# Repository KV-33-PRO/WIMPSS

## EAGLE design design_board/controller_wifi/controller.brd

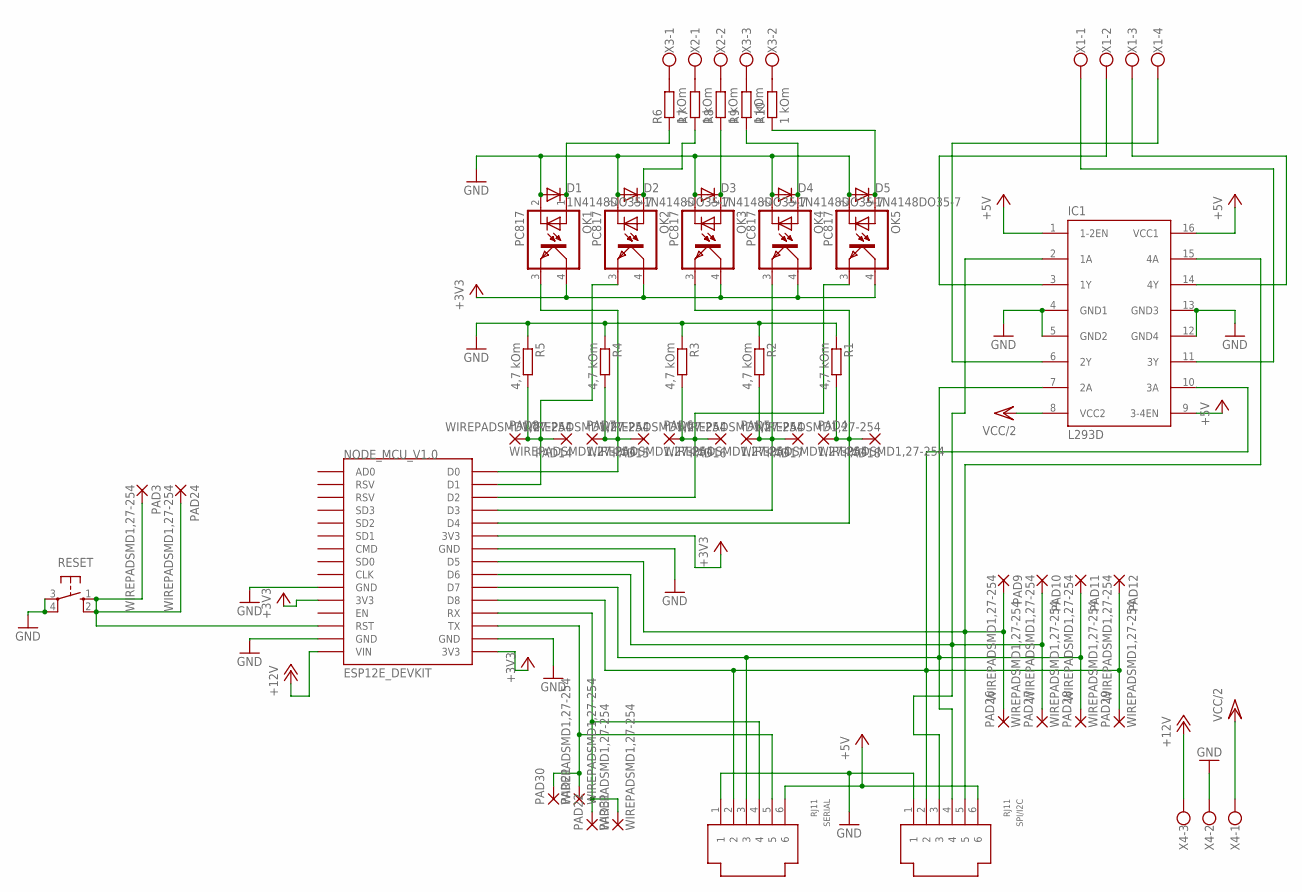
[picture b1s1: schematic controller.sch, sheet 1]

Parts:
D1, D2, D3, D4, D5: 1N4148DO35-7; DO35-7
IC1: L293D; DIL16
NODE_MCU_V1.0: ESP12E_DEVKIT
OK1, OK2, OK3, OK4, OK5: PC817; DIL04
PAD3, PAD4, PAD5, PAD6, PAD7, PAD8, PAD9, PAD10, PAD11, PAD12, PAD14, PAD15, PAD16, PAD17, PAD18, PAD21, PAD22, PAD24, PAD26, PAD27, PAD28, PAD29, PAD30, PAD31: WIREPADSMD1,27-254; SMD1,27-2,54
R1, R2, R3, R4, R5: 4,7 kOm; 0204/5
R6, R7, R8, R9, R10: 1 kOm; 0204V
RESET: 10-XX; B3F-10XX
SERIAL: RJ11
SPI/I2C: RJ11
X1: W237-4
X2: W237-102
X3, X4: W237-103

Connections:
+3V3: NODE_MCU_V1.0.3V3@0 (3V3), NODE_MCU_V1.0.3V3@1 (3V3), NODE_MCU_V1.0.3V3@2 (3V3), OK1.4 (COL), OK2.4 (COL), OK3.4 (COL), OK4.4 (COL), OK5.4 (COL); also elsewhere on the board
+5V: IC1.1 (1-2EN), IC1.9 (3-4EN), IC1.16 (VCC1), SERIAL.6, SPI/I2C.6; also elsewhere on the board
+12V: NODE_MCU_V1.0.VIN, X4.3; also elsewhere on the board
GND: D1.A, D2.A, D3.A, D4.A, D5.A, IC1.4 (GND1), IC1.5 (GND2), IC1.12 (GND4), IC1.13 (GND3), NODE_MCU_V1.0.GND@0 (GND), NODE_MCU_V1.0.GND@1 (GND), NODE_MCU_V1.0.GND@2 (GND), NODE_MCU_V1.0.GND@3 (GND), OK1.2 (C), OK2.2 (C), OK3.2 (C), OK4.2 (C), OK5.2 (C), R1.1, R2.1, R3.1, R4.1, R5.1, RESET.3, RESET.4 (P1), SERIAL.1, SPI/I2C.1, X4.2; also elsewhere on the board
unnamed: D4.C, OK4.1 (A), R9.1
unnamed: NODE_MCU_V1.0.D4, OK3.3 (EMIT), PAD4.1, PAD18.1, R1.2
unnamed: NODE_MCU_V1.0.D3, OK4.3 (EMIT), PAD5.1, PAD17.1, R2.2
unnamed: NODE_MCU_V1.0.D2, OK5.3 (EMIT), PAD6.1, PAD16.1, R3.2
unnamed: NODE_MCU_V1.0.D0, OK1.3 (EMIT), PAD7.1, PAD15.1, R4.2
unnamed: NODE_MCU_V1.0.D1, OK2.3 (EMIT), PAD8.1, PAD14.1, R5.2
unnamed: D2.C, OK2.1 (A), R7.1
unnamed: NODE_MCU_V1.0.RX, PAD22.1, PAD31.1, SERIAL.4
unnamed: D3.C, OK3.1 (A), R8.1
unnamed: R8.2, X2.2
unnamed: D5.C, OK5.1 (A), R10.1
unnamed: IC1.6 (2Y), X1.4
unnamed: IC1.7 (2A), NODE_MCU_V1.0.D7, PAD11.1, PAD28.1, SERIAL.3, SPI/I2C.4
unnamed: IC1.3 (1Y), X1.2
unnamed: IC1.10 (3A), NODE_MCU_V1.0.D8, PAD12.1, PAD29.1, SERIAL.2, SPI/I2C.2
unnamed: NODE_MCU_V1.0.TX, PAD21.1, PAD30.1, SERIAL.5
unnamed: IC1.2 (1A), NODE_MCU_V1.0.D6, PAD10.1, PAD27.1, SPI/I2C.3
unnamed: NODE_MCU_V1.0.RST, PAD3.1, PAD24.1, RESET.1 (S), RESET.2 (S1)
unnamed: IC1.15 (4A), NODE_MCU_V1.0.D5, PAD9.1, PAD26.1, SPI/I2C.5
unnamed: IC1.11 (3Y), X1.1
unnamed: IC1.14 (4Y), X1.3
unnamed: D1.C, OK1.1 (A), R6.1
unnamed: R7.2, X2.1
unnamed: R9.2, X3.3
unnamed: R10.2, X3.2
unnamed: R6.2, X3.1
VCC/2: IC1.8 (VCC2), X4.1; also elsewhere on the board

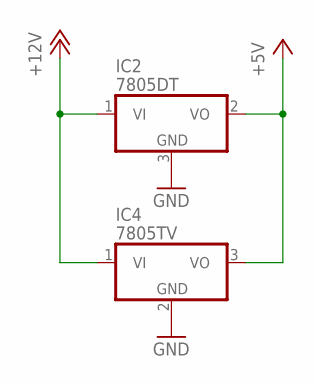
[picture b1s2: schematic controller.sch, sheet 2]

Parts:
IC2: 7805DT; TO252
IC4: 7805TV; TO220V

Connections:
+5V: IC2.2 (VO), IC4.3 (VO); also elsewhere on the board
+12V: IC2.1 (VI), IC4.1 (VI); also elsewhere on the board
GND: IC2.3 (GND), IC4.2 (GND); also elsewhere on the board

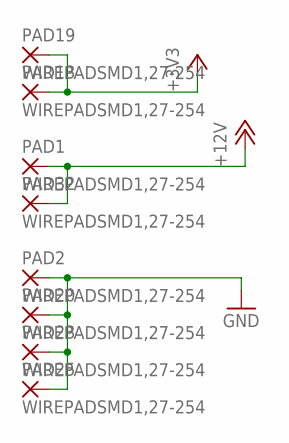
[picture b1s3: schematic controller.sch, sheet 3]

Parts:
PAD1, PAD2, PAD13, PAD19, PAD20, PAD23, PAD25, PAD32: WIREPADSMD1,27-254; SMD1,27-2,54

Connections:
+3V3: PAD13.1, PAD19.1; also elsewhere on the board
+12V: PAD1.1, PAD32.1; also elsewhere on the board
GND: PAD2.1, PAD20.1, PAD23.1, PAD25.1; also elsewhere on the board

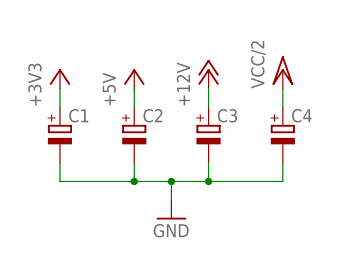
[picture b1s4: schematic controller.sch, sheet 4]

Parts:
C1, C2, C3, C4: CPOL-EUE2.5-5; E2,5-5

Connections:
+3V3: C1.+; also elsewhere on the board
+5V: C2.+; also elsewhere on the board
+12V: C3.+; also elsewhere on the board
GND: C1.-, C2.-, C3.-, C4.-; also elsewhere on the board
VCC/2: C4.+; also elsewhere on the board

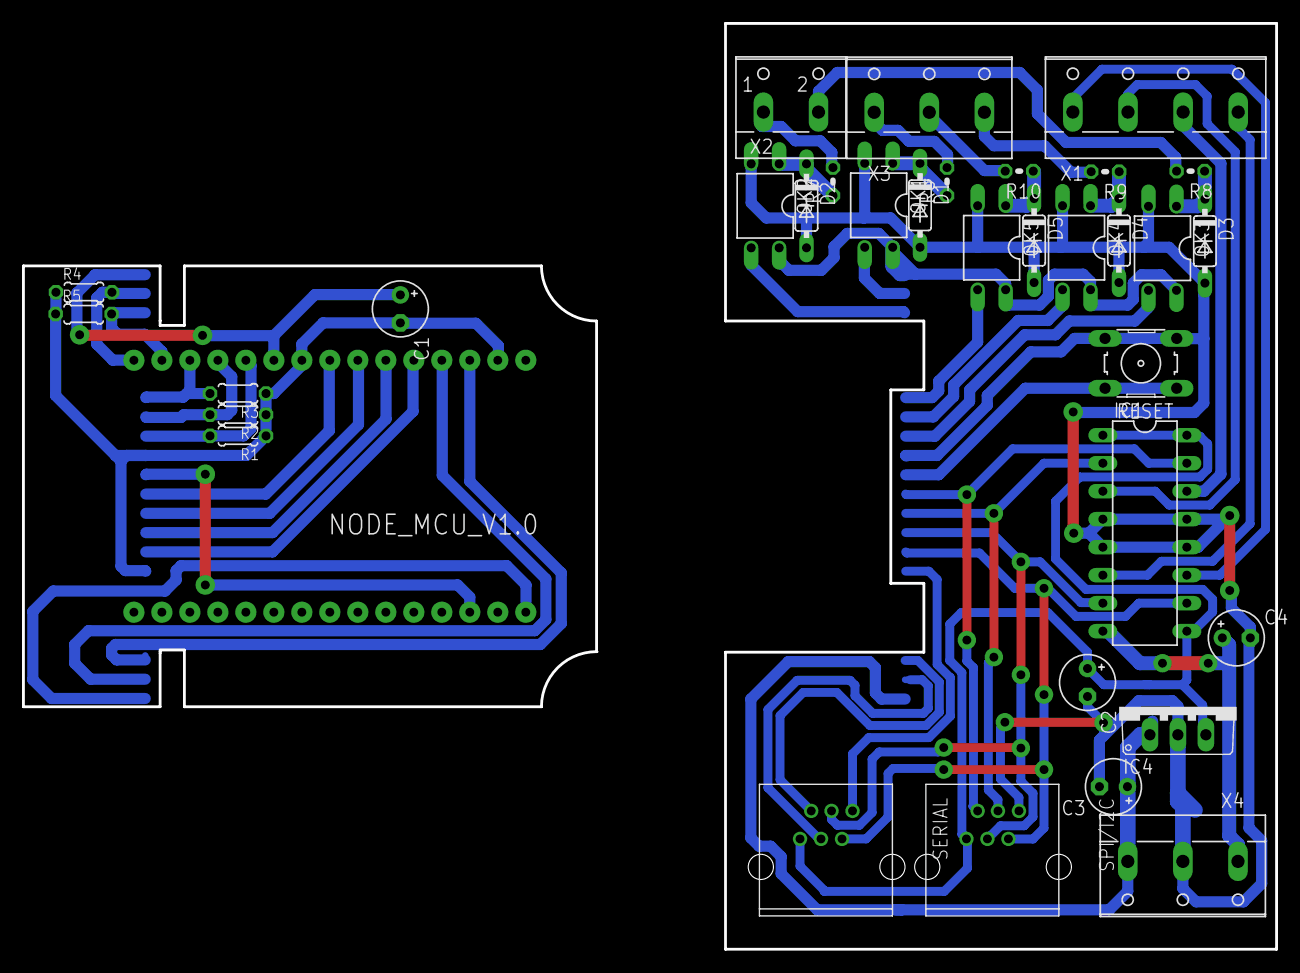
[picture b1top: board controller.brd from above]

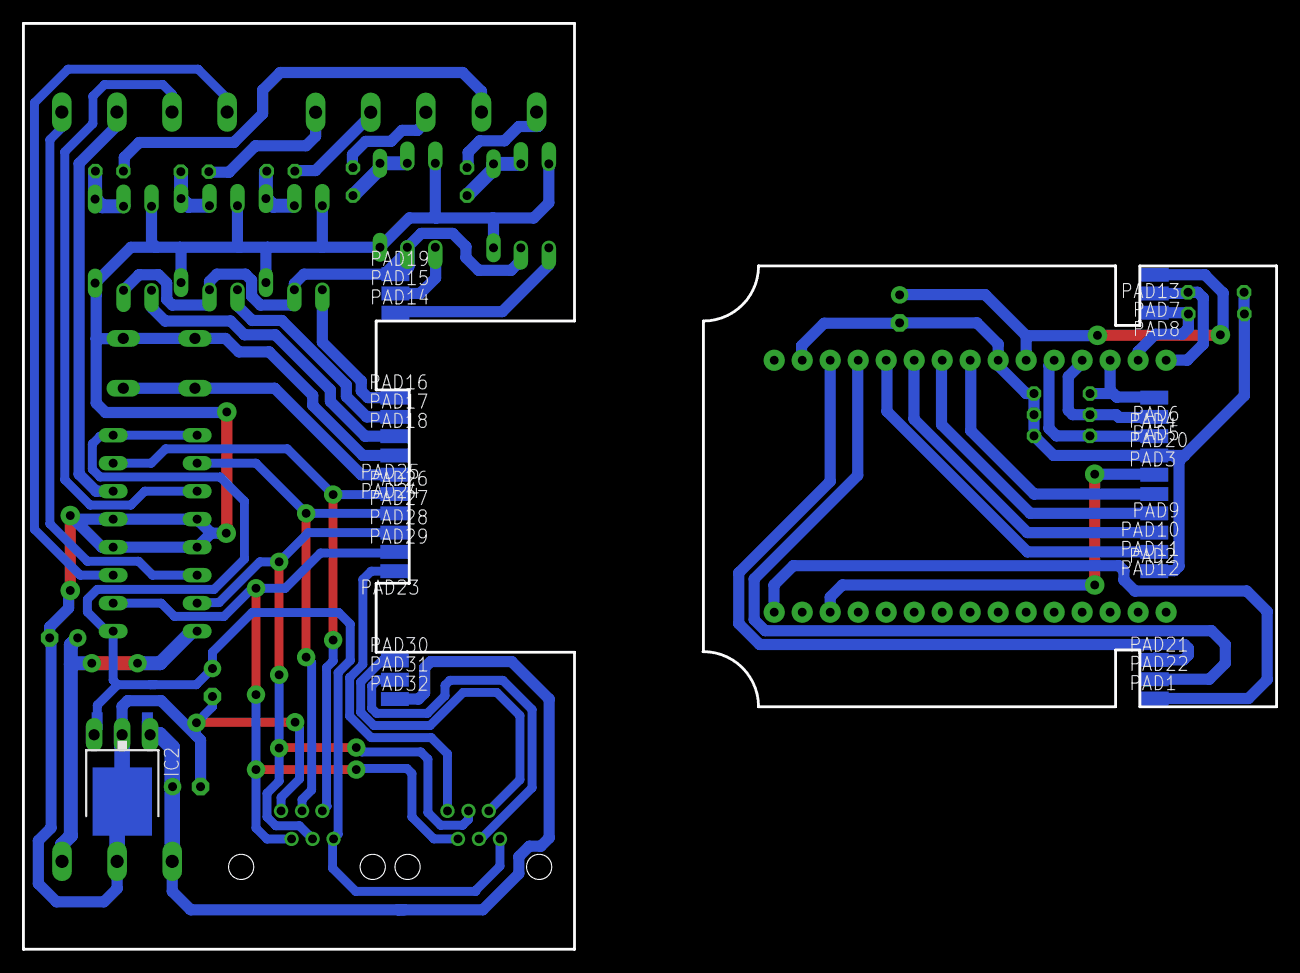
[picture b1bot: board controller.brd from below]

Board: 2 copper layers, 113.7 x 84.0 mm, 67 parts (33 on the bottom side), 31 nets.

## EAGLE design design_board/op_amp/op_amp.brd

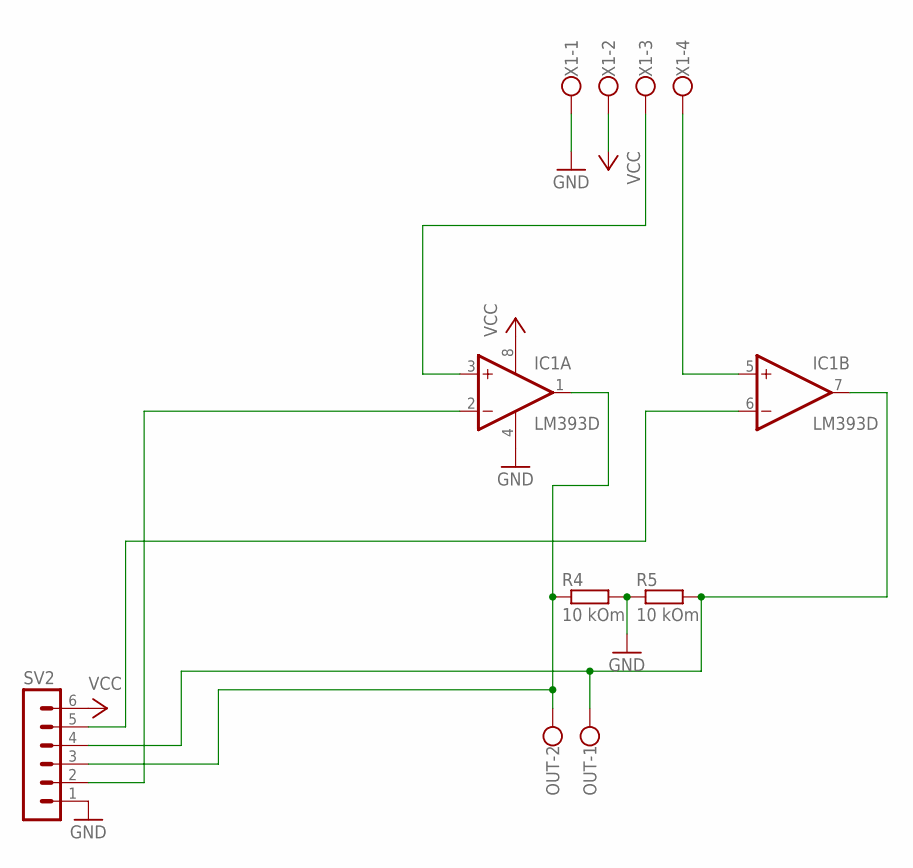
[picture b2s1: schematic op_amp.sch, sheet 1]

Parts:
IC1: LM393D; SO08
OUT: W237-102
R4, R5: 10 kOm; 0207/7
SV2: MA06-1
X1: W237-4

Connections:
GND: IC1.4 (V-), R4.2, R5.1, SV2.1, X1.1; also elsewhere on the board
unnamed: IC1.6 (-IN), SV2.5
unnamed: IC1.1 (OUT), OUT.2, R4.1, SV2.3
unnamed: IC1.3 (+IN), X1.3
unnamed: IC1.5 (+IN), X1.4
unnamed: IC1.2 (-IN), SV2.2
unnamed: IC1.7 (OUT), OUT.1, R5.2, SV2.4
VCC: IC1.8 (V+), SV2.6, X1.2; also elsewhere on the board

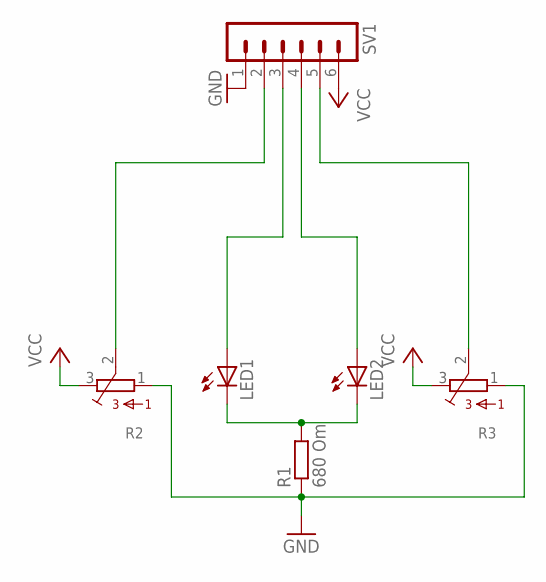
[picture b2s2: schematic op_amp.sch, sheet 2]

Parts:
LED1, LED2: LED3MM
R1: 680 Om; 0207/7
R2, R3: 3362P
SV1: MA06-1

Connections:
GND: R1.1, R2.1, R3.1, SV1.1; also elsewhere on the board
unnamed: LED1.A, SV1.3
unnamed: LED1.K (C), LED2.K (C), R1.2
unnamed: LED2.A, SV1.4
unnamed: R3.2, SV1.5
unnamed: R2.2, SV1.2
VCC: R2.3, R3.3, SV1.6; also elsewhere on the board

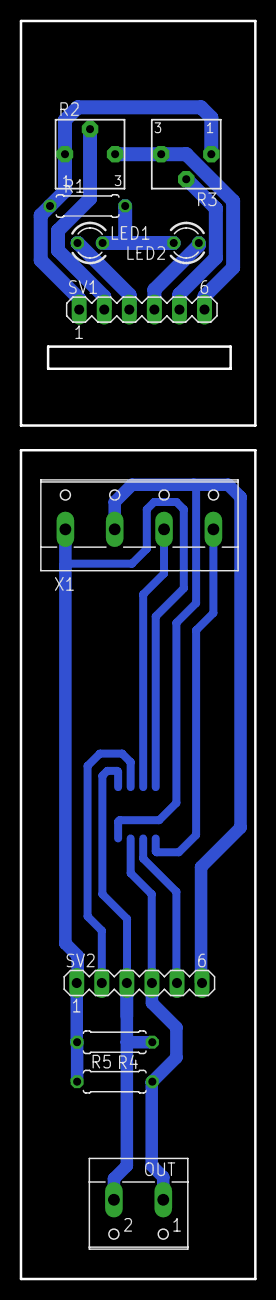
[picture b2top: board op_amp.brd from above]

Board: 2 copper layers, 23.8 x 127.5 mm, 12 parts (1 on the bottom side), 13 nets.

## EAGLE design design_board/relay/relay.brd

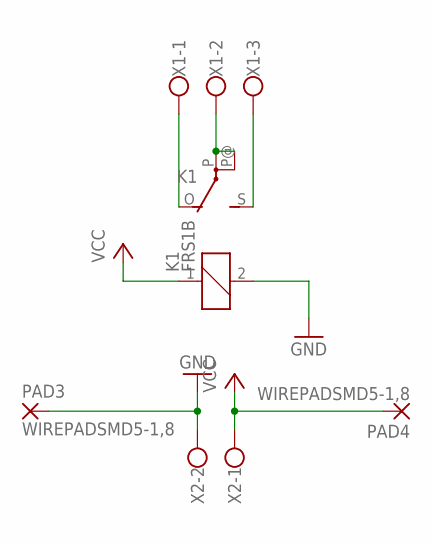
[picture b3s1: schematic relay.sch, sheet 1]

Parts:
K1: FRS1B
PAD3, PAD4: WIREPADSMD5-1,8; 5-1,8
X1: W237-103
X2: W237-102

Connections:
GND: K1.2, PAD3.1, X2.2
unnamed: K1.O, X1.1
unnamed: K1.S, X1.3
unnamed: K1.P, K1.P@, X1.2
VCC: K1.1, PAD4.1, X2.1

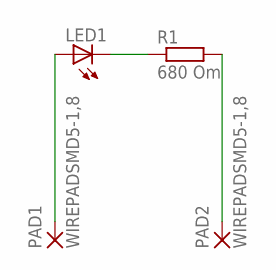
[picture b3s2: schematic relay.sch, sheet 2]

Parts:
LED1: LED3MM
PAD1, PAD2: WIREPADSMD5-1,8; 5-1,8
R1: 680 Om; 0207/7

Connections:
GND_LED: PAD2.1, R1.2
unnamed: LED1.K (C), R1.1
VCC_LED: LED1.A, PAD1.1

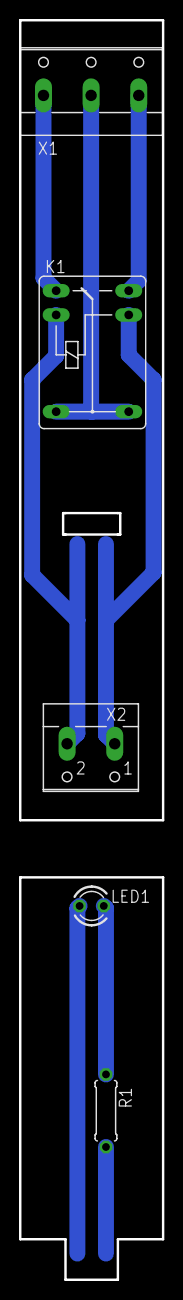
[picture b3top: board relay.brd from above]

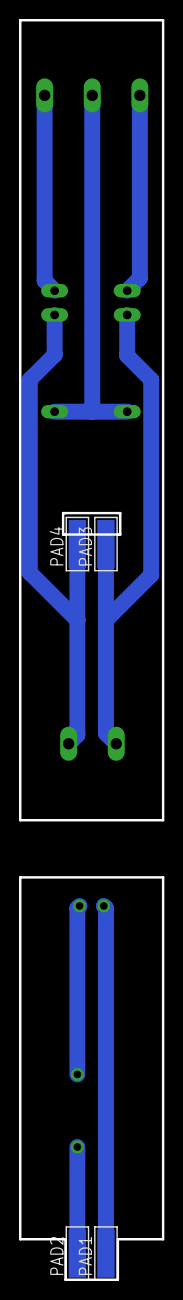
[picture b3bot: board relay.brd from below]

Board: 2 copper layers, 15.0 x 132.2 mm, 9 parts (4 on the bottom side), 8 nets.

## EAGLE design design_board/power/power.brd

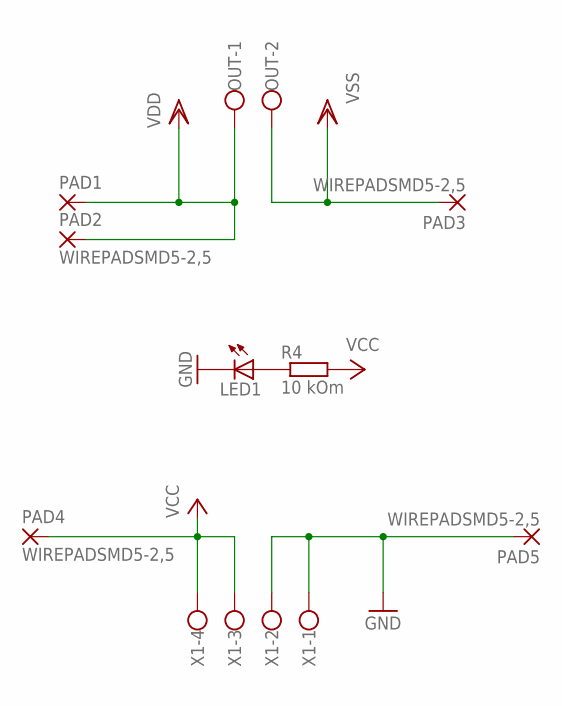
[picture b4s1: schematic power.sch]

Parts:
LED1: LED3MM
OUT: W237-102
PAD1: 2,54/1,0
PAD2, PAD3, PAD4, PAD5: WIREPADSMD5-2,5; 5-2,5
R4: 10 kOm; 0207/7
X1: W237-4

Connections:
GND: LED1.K (C), PAD5.1, X1.1, X1.2
unnamed: LED1.A, R4.1
VCC: PAD4.1, R4.2, X1.3, X1.4
VDD: OUT.1, PAD1.1, PAD2.1
VSS: OUT.2, PAD3.1

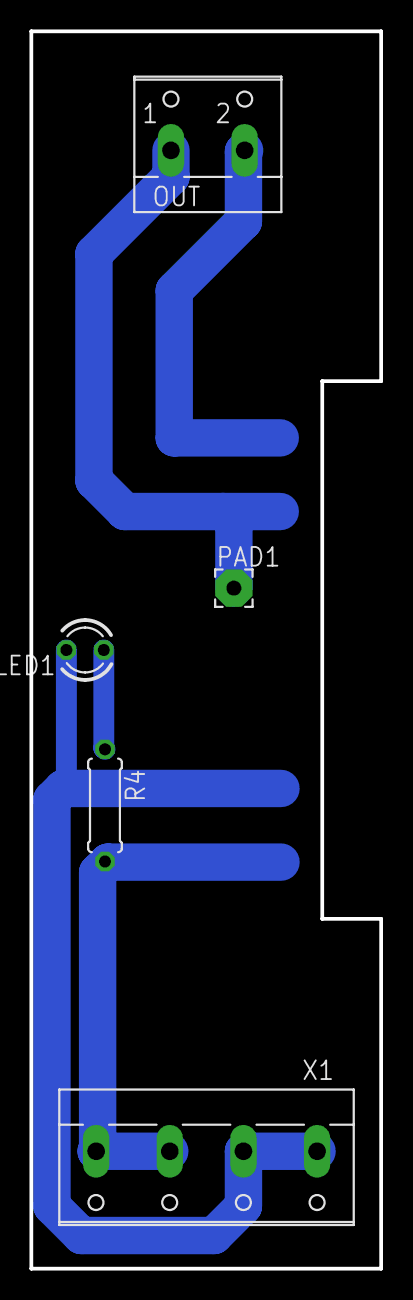
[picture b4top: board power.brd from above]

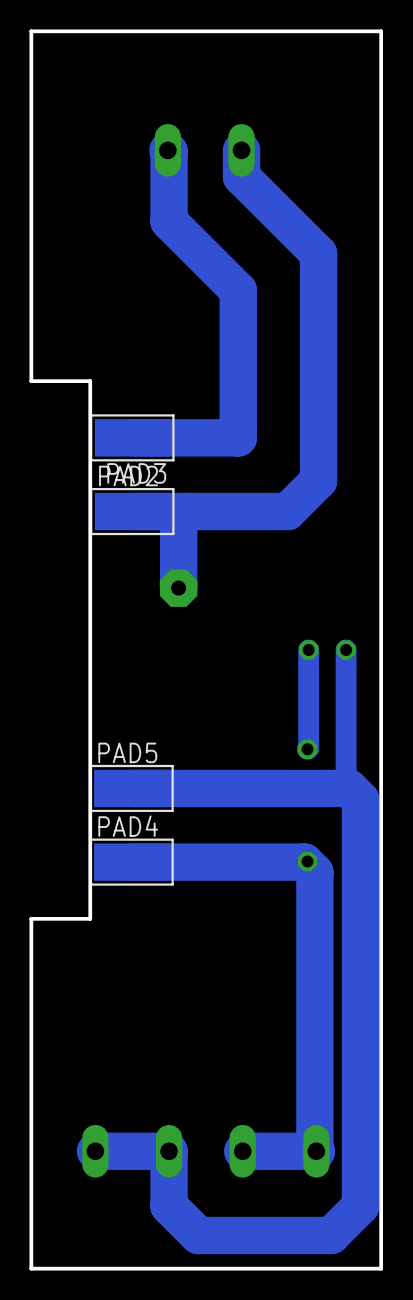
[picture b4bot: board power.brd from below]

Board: 2 copper layers, 23.8 x 84.0 mm, 9 parts (4 on the bottom side), 5 nets.

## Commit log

2019-04-12 Добавлен модуль реле (эл. схема и плата)
2019-04-16 Добавлен модуль контроллера с wifi (эл. схема и плата)
2019-04-16 Изменен модуль контроллера с wifi (добавлены выемки для мест сборки корпуса)
2019-04-16 Изменен модуль контроллера с wifi (добавлены конденсаторы на линии питания, резисторы на входе - перед оптопарами)
2019-04-23 Изменен модуль контроллера с wifi (заменены разъемы RJ-11, увеличина толщина дорожек), добавлены используемые библиотеки.
2019-04-23 Изменен модуль контроллера с wifi (убраны отверстия с NodeMCU), добавлена библиотека NodeMCU без крепежных отверстий.
2019-05-01 Добавлен модуль операционного усилителя (эл. схема и плата)
2019-05-01 Добавлен модуль питания (эл. схема и плата)
2019-05-14 Изменены платы controller.brd и relay.brd - скорректированы зазоры между платами, оp_amp.brd - добавлено отверстие для прокладки проводки между уровнями. Изменена схема сontroller.sch - добавлены ном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
